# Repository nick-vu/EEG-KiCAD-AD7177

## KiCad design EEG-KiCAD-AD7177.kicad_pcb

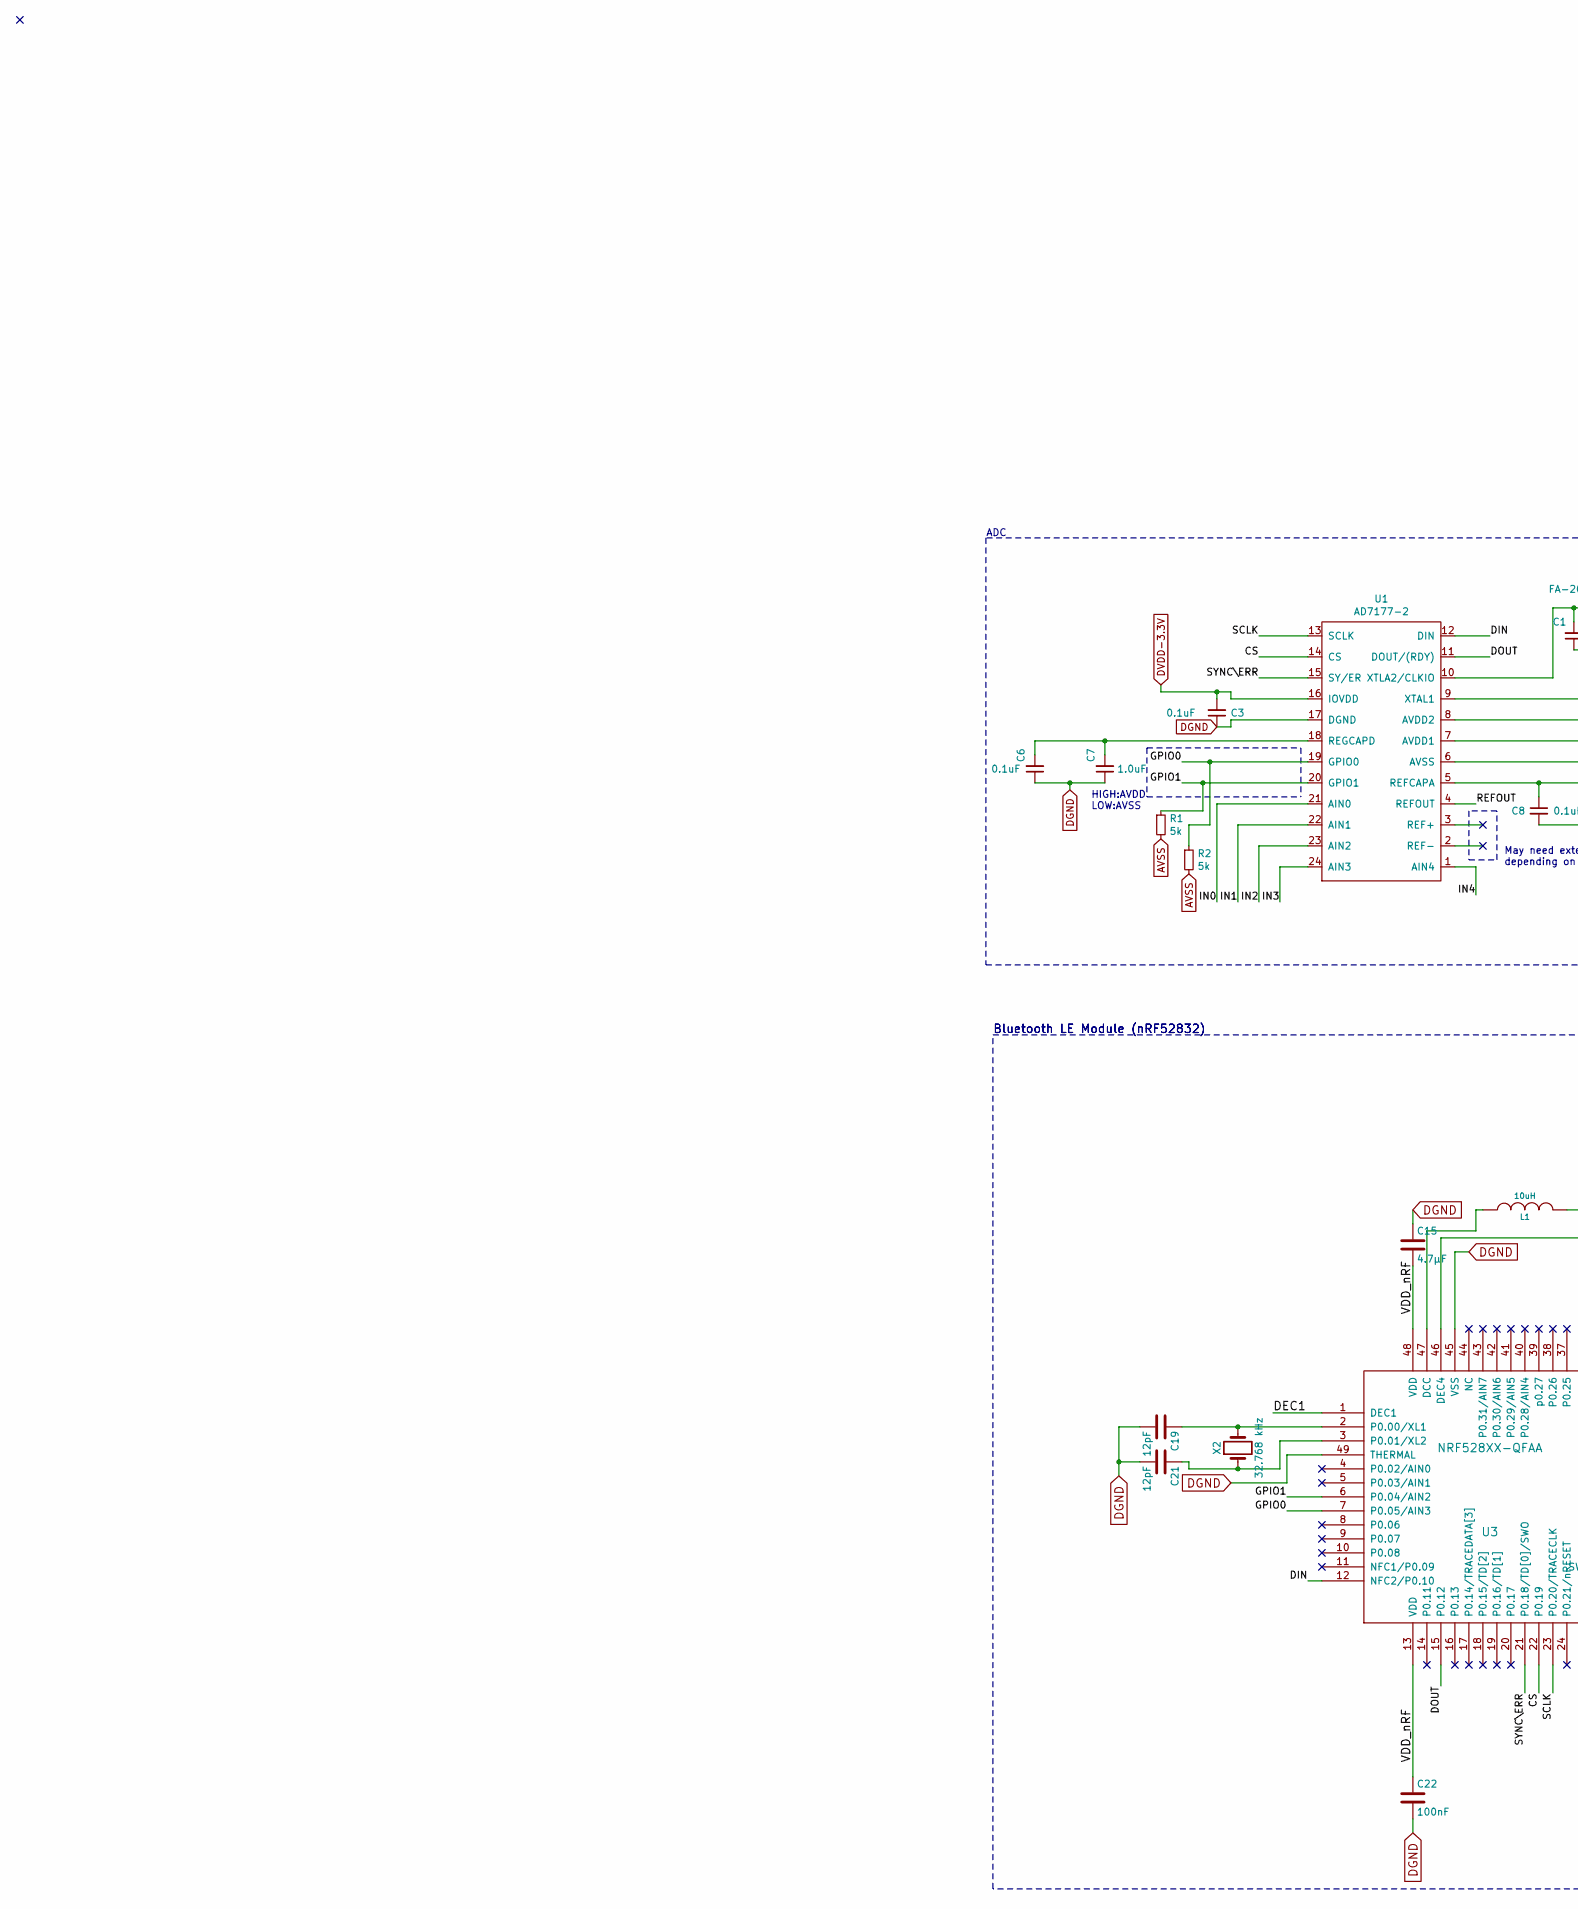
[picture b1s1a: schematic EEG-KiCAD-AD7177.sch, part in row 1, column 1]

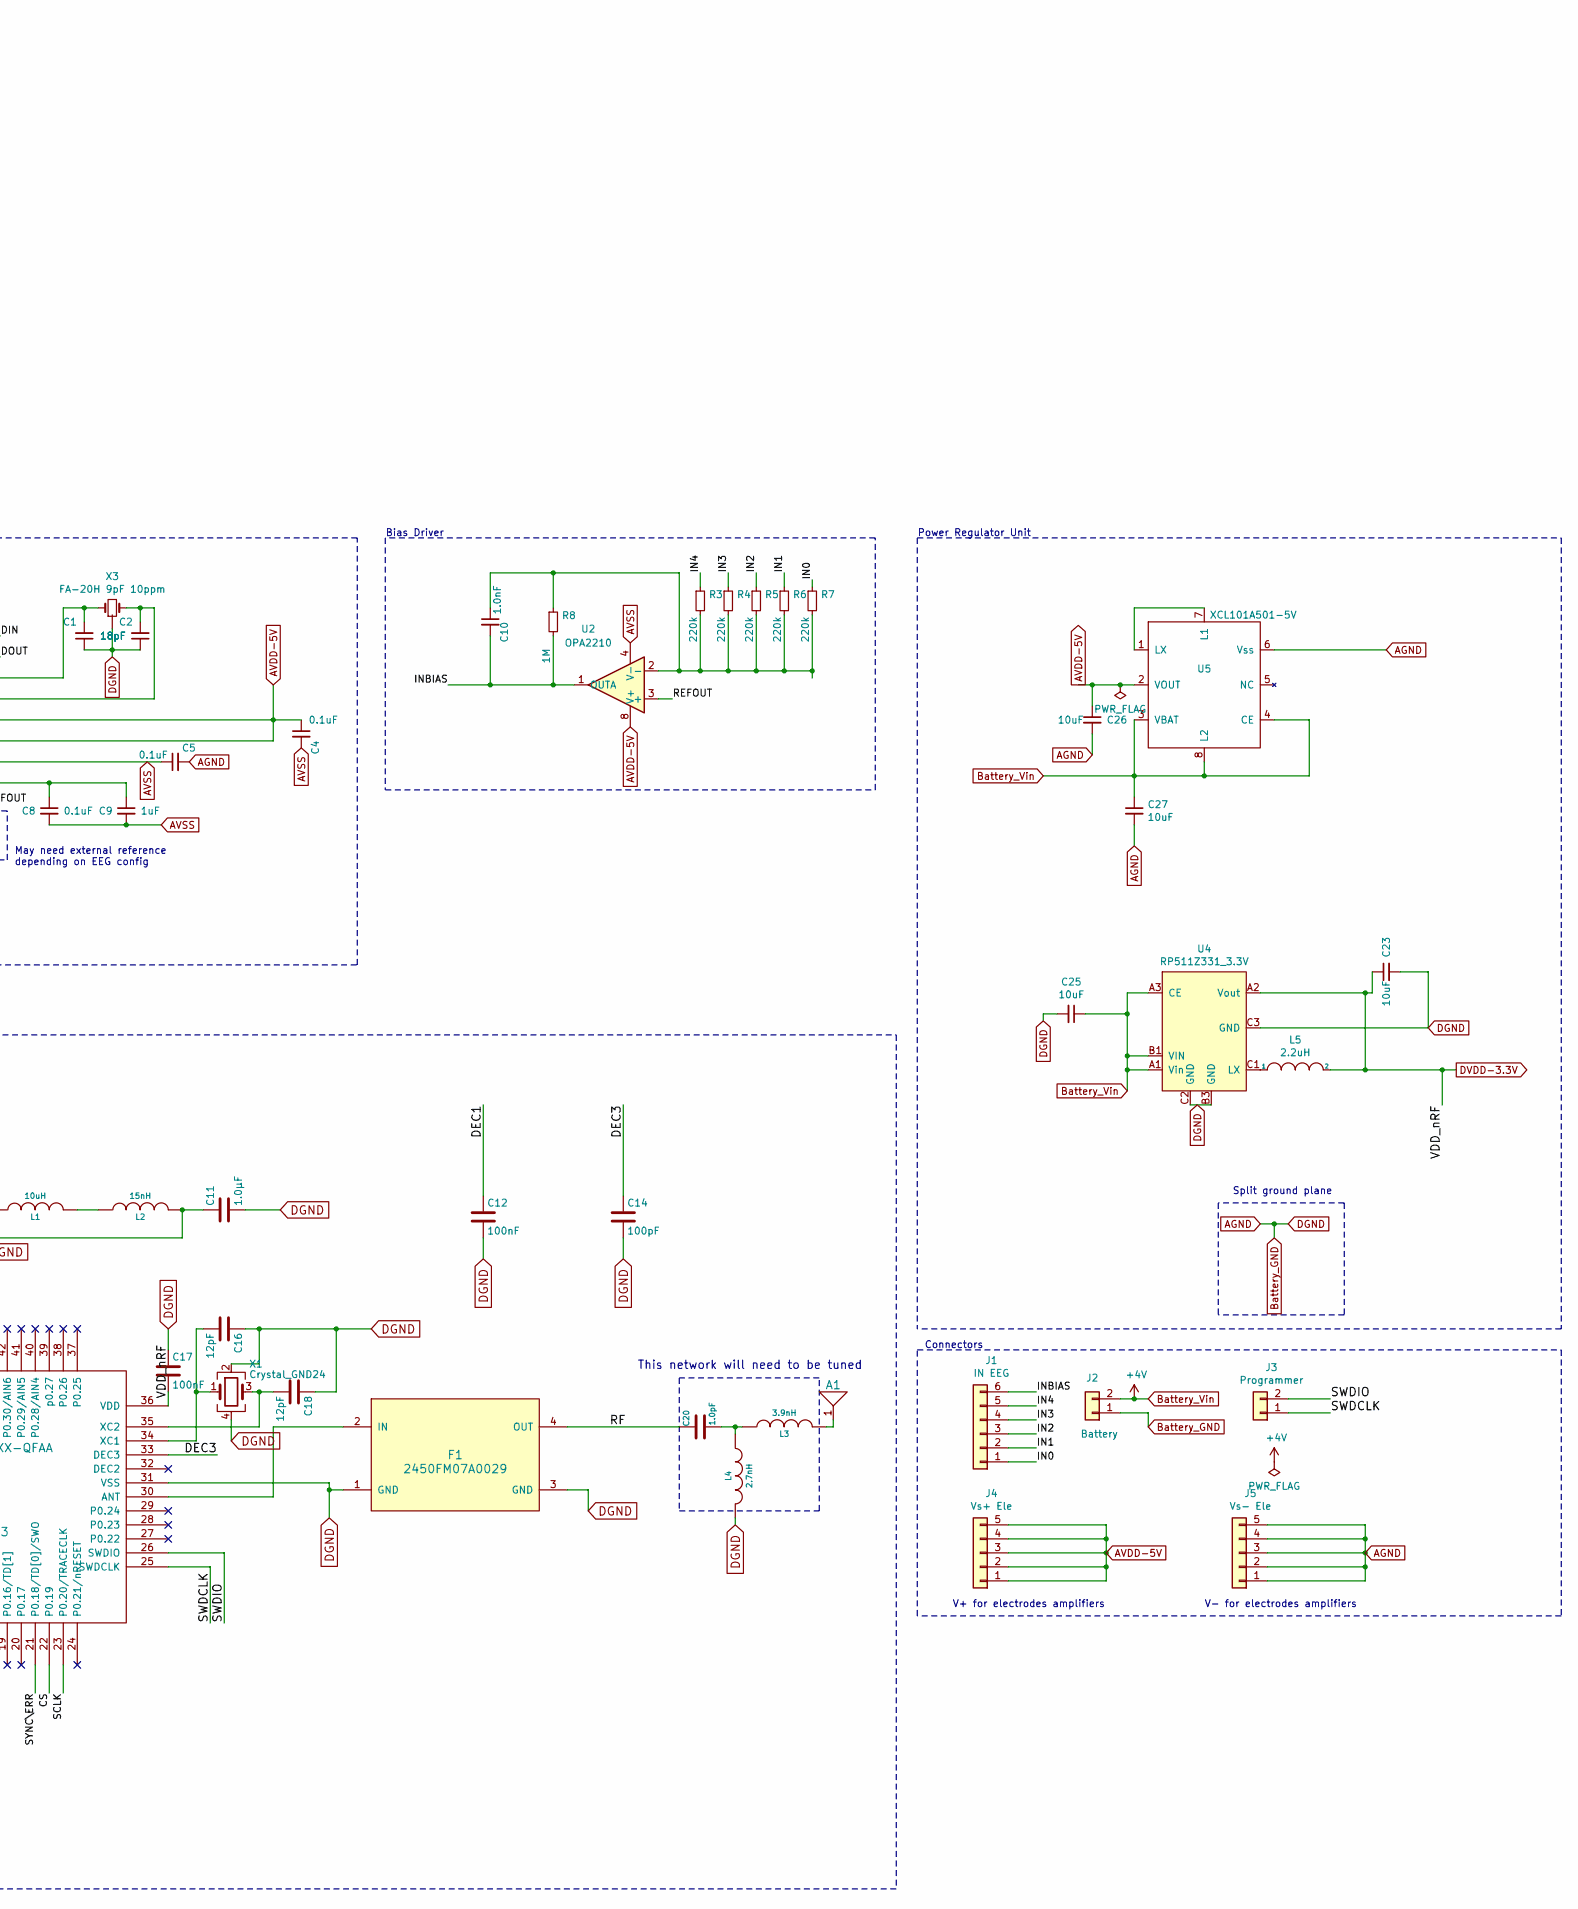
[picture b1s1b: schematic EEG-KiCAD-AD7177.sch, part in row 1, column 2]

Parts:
A1: CHIP-ANT; JTI-2450AT18A100-CHIP-ANT
C1, C2: 18pF; C_0402_1005Metric
C3, C4, C5, C6, C8: 0.1uF; C_0402_1005Metric
C7: 1.0uF; C_0402_1005Metric
C9: 1uF; C_0402_1005Metric
C10: 1.0nF; C_0402_1005Metric
C11: 1.0µF; C_0402_1005Metric
C12, C17, C22: 100nF; C_0402_1005Metric
C14: 100pF; C_0402_1005Metric
C15: 4.7µF; C_0402_1005Metric
C16, C18, C19, C21: 12pF; C_0402_1005Metric
C20: 1.0pF; C_0402_1005Metric
C23, C25, C26, C27: 10uF; C_0402_1005Metric
F1: 2450FM07A0029; Modified_cap-0402-ground
J1: IN EEG; PinHeader_1x06_P2.54mm_Vertical
J2: Battery; PinHeader_1x02_P2.54mm_Vertical
J3: Programmer; PinHeader_1x02_P2.54mm_Vertical
J4: Vs+ Ele; PinHeader_1x05_P2.54mm_Vertical
J5: Vs- Ele; PinHeader_1x05_P2.54mm_Vertical
L1: 10uH; L_0603_1608Metric
L2: 15nH; L_0402_1005Metric
L3: 3.9nH; L_0402_1005Metric
L4: 2.7nH; L_0402_1005Metric
L5: 2.2uH; L_0603_1608Metric
R1, R2: 5k; R_0402_1005Metric
R3, R4, R5, R6, R7: 220k; R_0402_1005Metric
R8: 1M; R_0603_1608Metric
U1: AD7177-2; SOP65P640X120-24N
U2: OPA2210; VSSOP-8_3.0x3.0mm_P0.65mm
U3: NRF528XX-QFAA; UQFN-48-1EP_6x6mm_Pitch0.4mm
U4: RP511Z331_3.3V; RP511Z331
U5: XCL101A501-5V; CONV_XCL206B333CR-G
X1: Crystal_GND24; Crystal_SMD_2016-4pin_2.0x1.6mm
X2: 32.768 kHz; Crystal_SMD_2012-2Pin_2.0x1.2mm
X3: FA-20H 9pF 10ppm; Crystal_SMD_2520-4Pin_2.5x2.0mm

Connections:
/CS: U1.14 (CS), U3.22 (P0.19)
/DEC1: C12.1, U3.1 (DEC1)
/DEC3: C14.1, U3.33 (DEC3)
/DIN: U1.12 (DIN), U3.12 (NFC2/P0.10)
/DOUT: U1.11 (DOUT/(RDY)), U3.15 (P0.12)
/GPIO0: R2.1, U1.19 (GPIO0), U3.7 (P0.05/AIN3)
/GPIO1: R1.1, U1.20 (GPIO1), U3.6 (P0.04/AIN2)
/IN0: J1.1, R7.1, U1.21 (AIN0)
/IN1: J1.2, R6.1, U1.22 (AIN1)
/IN2: J1.3, R5.1, U1.23 (AIN2)
/IN3: J1.4, R4.1, U1.24 (AIN3)
/IN4: J1.5, R3.1, U1.1 (AIN4)
/INBIAS: C10.2, J1.6, R8.2, U2.1 (OUTA~)
/REFOUT: U1.4 (REFOUT), U2.3 (+)
/RF: C20.1, F1.4 (OUT)
/SCLK: U1.13 (SCLK), U3.23 (P0.20/TRACECLK)
/SWDCLK: J3.1, U3.25 (SWDCLK)
/SWDIO: J3.2, U3.26 (SWDIO)
/SYNC\ERR: U1.15 (SY/ER), U3.21 (P0.18/TD[0]/SWO)
AGND: C1.1, C2.1, C3.1, C5.2, C6.1, C7.1, C11.2, C12.2, C14.2, C15.1, C16.1, C17.1, C18.1, C19.2, C21.2, C22.2, C23.2, C25.2, C26.2, C27.2, F1.1 (GND), F1.3 (GND), J2.1, J5.1, J5.2, J5.3, J5.4, J5.5, L4.2, U1.17 (DGND), U3.31 (VSS), U3.45 (VSS), U3.49 (THERMAL), U4.B3 (GND), U4.C2 (GND), U4.C3 (GND), U5.6 (Vss), X1.2, X1.4, X3.2 (GND), X3.4 (GND)
AVDD-5V: C4.1, C26.1, J4.1, J4.2, J4.3, J4.4, J4.5, U1.7 (AVDD1), U1.8 (AVDD2), U2.8 (V+), U5.2 (VOUT)
AVSS: C4.2, C5.1, C8.2, C9.2, R1.2, R2.2, U1.6 (AVSS), U2.4 (V-)
Battery_Vin: C25.1, C27.1, J2.2, U4.A1 (Vin), U4.A3 (CE), U4.B1 (VIN), U5.3 (VBAT), U5.4 (CE), U5.8 (L2)
DVDD-3.3V: C3.2, C15.2, C17.2, C22.1, C23.1, L5.2, U1.16 (IOVDD), U3.13 (VDD), U3.36 (VDD), U3.48 (VDD), U4.A2 (Vout)
unnamed: A1.1 (ANT), L3.2
unnamed: C1.2, U1.10 (XTLA2/CLKIO), X3.1
unnamed: C2.2, U1.9 (XTAL1), X3.3 (2)
unnamed: C6.2, C7.2, U1.18 (REGCAPD)
unnamed: C8.1, C9.1, U1.5 (REFCAPA)
unnamed: C10.1, R3.2, R4.2, R5.2, R6.2, R7.2, R8.1, U2.2 (-)
unnamed: C11.1, L2.2, U3.46 (DEC4)
unnamed: C16.2, U3.34 (XC1), X1.1
unnamed: C18.2, U3.35 (XC2), X1.3
unnamed: C19.1, U3.2 (P0.00/XL1), X2.2
unnamed: C20.2, L3.1, L4.1
unnamed: C21.1, U3.3 (P0.01/XL2), X2.1
unnamed: F1.2 (IN), U3.30 (ANT)
unnamed: L1.1, U3.47 (DCC)
unnamed: L1.2, L2.1
unnamed: L5.1, U4.C1 (LX)
unnamed: U5.1 (LX), U5.7 (L1)

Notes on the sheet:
This network will need to be tuned
Bluetooth LE Module (nRF52832)
May need external reference depending on EEG config
HIGH:AVDD LOW:AVSS
Bias Driver
ADC
Power Regulator Unit
Connectors
Split ground plane
V+ for electrodes amplifiers
V- for electrodes amplifiers

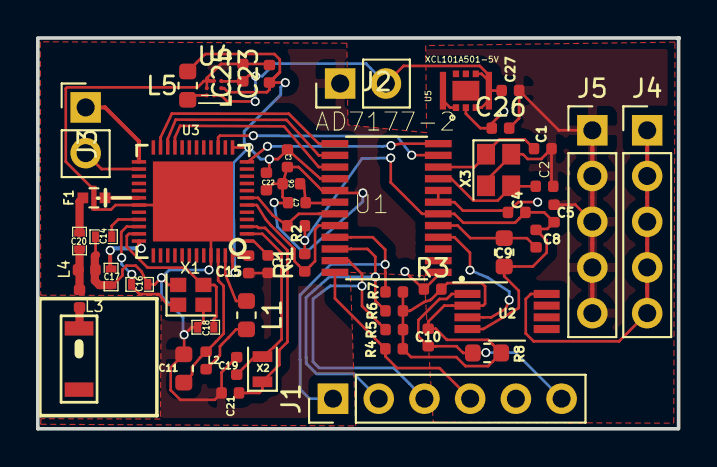
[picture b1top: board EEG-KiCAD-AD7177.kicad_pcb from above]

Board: 2 copper layers, 35.6 x 21.7 mm, 53 parts (0 on the bottom side), 41 nets.

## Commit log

2019-04-11 Changed with added voltage source
2019-04-11 DOne
2019-04-17 With description
2019-04-30 Fixed pins
    Fixed wrong pins
